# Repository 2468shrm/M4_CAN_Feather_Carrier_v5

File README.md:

# M4_CAN_Feather_Carrier_v5

## Board Layout

## Changes from Previous M4 Carrier Boards

This board has undergone multiple changes from previous versions of thie board, including, but not limite to:
- The level shifter for the DIOs was changed to the TXS0104B from the TXB version
  - The TXS version includes built-in pull ups and works considerably more reliably
- LEDs were added to indicate the logical state of the DIOs
  - An LED was added to each DIO as well as the level shifter enable
- The unity gain opamp was chaged to the LMV324AIDR which is a rail-to-rail version of the prior opamp
- One Qwiic/STEMMA port is removed (leaving 3)
- A MicroSD socket is added and extended to the SPI network (which now comprises of the Ethernet FeatherWing and the MicroS socket)
- A DC-DC converter is adde to the PCB replacing the Weewoodday module (woohoo)
- Cost reduced
  - Replaced many components with JLCPCB "Basic Parts" to reduce the Extended Parts costs
  - Many are 0603 devices for use with JLCPCB's PCBA service
- Updated the silkscreen to congratulate Unni Peri's graduation (the team will miss her contributions in the future, we're sure)

A PDF copy of the schematic [here](https://github.com/2468shrm/M4_CAN_Feather_Carrier_v3/blob/main/Images/Schematic.pdf).

## Checkout Status

This board has bot been fabbed yet.

Not yet tested:
- Everything :)

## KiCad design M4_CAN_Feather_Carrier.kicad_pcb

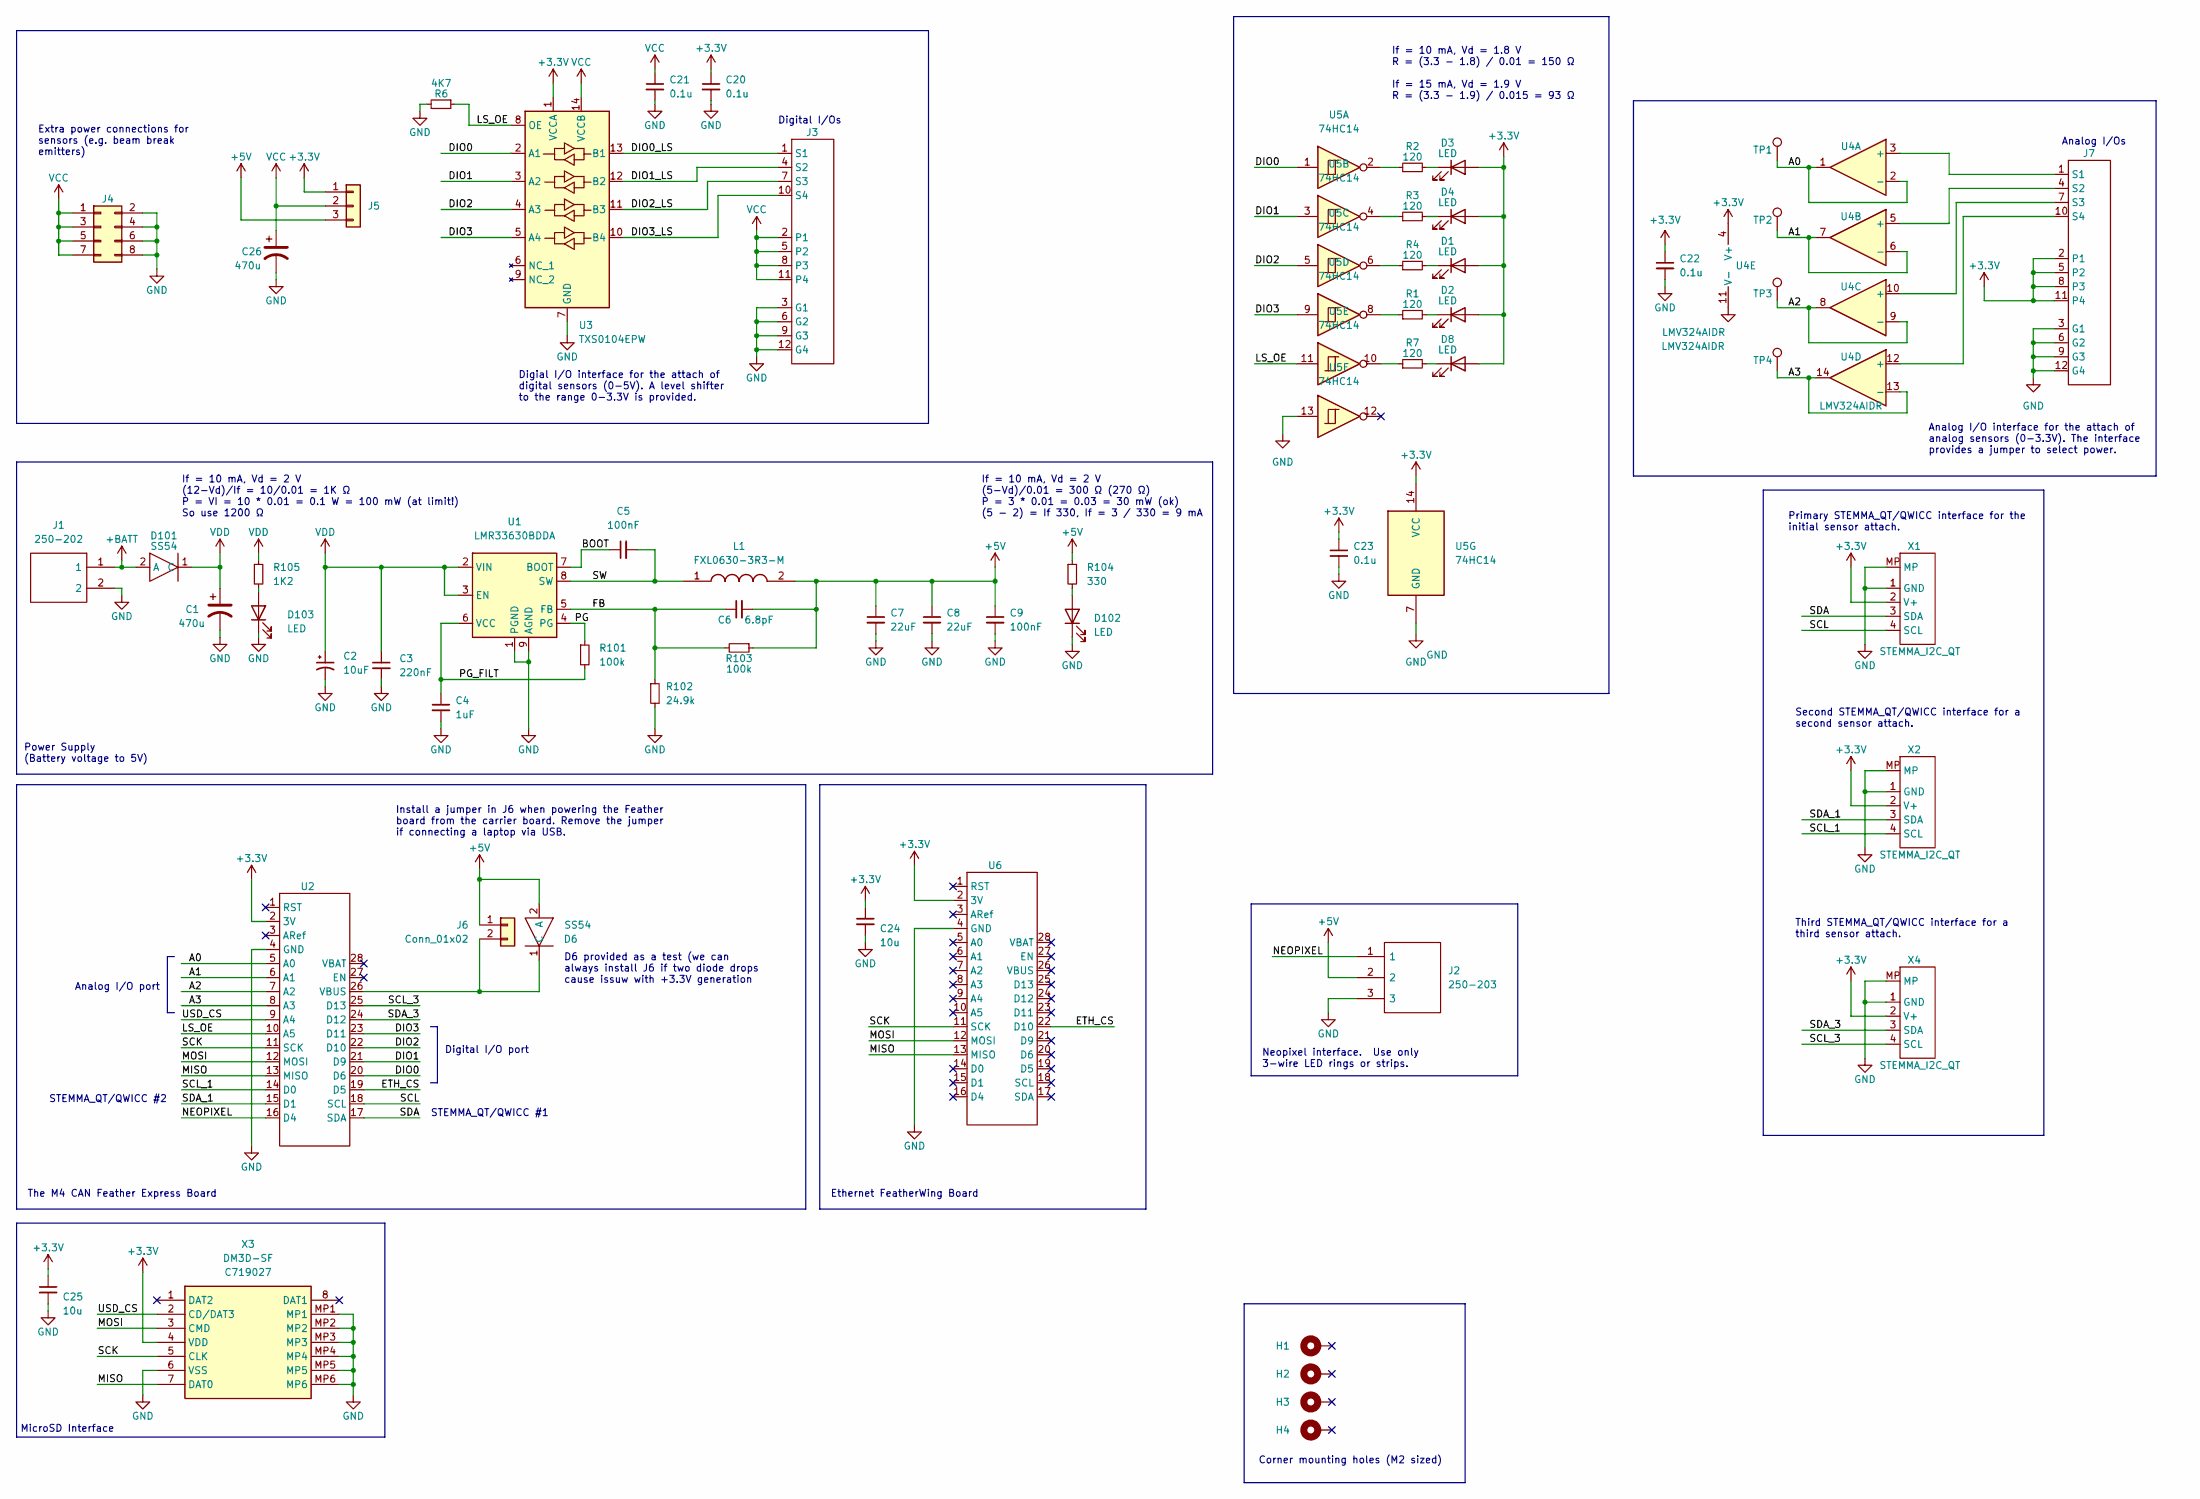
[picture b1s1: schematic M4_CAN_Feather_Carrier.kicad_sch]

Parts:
C1, C26: 470u; CAPAE830X1050N; LCSC C340767
C2: 10uF; C_0603_1608Metric; LCSC C96446
C3: 220nF; C_0603_1608Metric; LCSC C21120
C4: 1uF; C_0603_1608Metric; LCSC C59302
C5, C9: 100nF; C_0603_1608Metric; LCSC C14663
C6: 6.8pF; C_0603_1608Metric; LCSC C1679
C7, C8: 22uF; C_0805_2012Metric; LCSC C45783
C20, C21, C22, C23: 0.1u; C_0603_1608Metric; LCSC C14663
C24, C25: 10u; C_0603_1608Metric; LCSC C96446
D1, D2, D3, D4, D8, D102, D103: LED; LED_0603_1608Metric; LCSC C2286
D6, D101: SS54; DO-214AC; LCSC C22452
H1, H2, H3, H4: MountingHole_Pad; MountingHole_2.2mm_M2_DIN965_Pad
J1: 250-202; 250202; Manufacturer_Part_Number 250-202
J2: 250-203; 250-203_1; Manufacturer_Part_Number 250-203
J3, J7: conn_04_03; conn_04x03
J4: Conn_02x04_Odd_Even; PinHeader_2x04_P2.54mm_Vertical
J5: Conn_01x03; PinHeader_1x03_P2.54mm_Vertical
J6: Conn_01x02; PinHeader_1x02_P2.54mm_Vertical
L1: FXL0630-3R3-M; FXL0630; Manufacturer_Part_Number ASPI-0804T-150M-T; LCSC C167219
R1, R2, R3, R4, R7: 120; R_0603_1608Metric; LCSC C22787
R6: 4K7; R_0603_1608Metric; LCSC C23162
R101, R103: 100k; R_0603_1608Metric; LCSC C25803
R102: 24.9k; R_0603_1608Metric; LCSC C25962
R104: 330; R_0603_1608Metric; LCSC C23138
R105: 1K2; R_0603_1608Metric; LCSC C22765
TP1, TP2, TP3, TP4: TestPoint; TestPoint_Pad_1.5x1.5mm
U1: LMR33630BDDA; Texas_HSOP-8-1EP_3.9x4.9mm_P1.27mm_ThermalVias; LCSC C544370
U2, U6: Feather_M4_CAN_Express
U3: TXS0104EPW; TSSOP-14_4.4x5mm_P0.65mm; LCSC C44955
U4: LMV324AIDR; SOIC-14_3.9x8.7mm_P1.27mm; LCSC C484732
U5: 74HC14; TSSOP-14_4.4x5mm_P0.65mm; LCSC C2866133
X1, X2, X4: STEMMA_I2C_QT; JST_SH_BM04B-SRSS-TB_1x04-1MP_P1.00mm_Vertical; LCSC C495539
X3: DM3D-SF; DM3DSF; Manufacturer_Part_Number DM3D-SF; Mouser Part Number 798-DM3D-SF

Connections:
+3.3V: C20.1, C22.1, C23.1, C24.1, C25.1, D1.2 (A), D2.2 (A), D3.2 (A), D4.2 (A), D8.2 (A), J5.1, J7.2 (P1), J7.5 (P2), J7.8 (P3), J7.11 (P4), U2.2 (3V), U3.1 (VCCA), U4.4 (V+), U5.14 (VCC), U6.2 (3V), X1.2 (V+), X2.2 (V+), X3.4 (VDD), X4.2 (V+)
+5V: C6.2, C7.1, C8.1, C9.1, D6.2 (A), J2.2, J5.3, J6.1, L1.2, R103.1, R104.1
+BATT: D101.2 (A), J1.1
/A0: TP1.1, U2.5 (A0), U4.1, U4.2 (-)
/A1: TP2.1, U2.6 (A1), U4.6 (-), U4.7
/A2: TP3.1, U2.7 (A2), U4.8, U4.9 (-)
/A3: TP4.1, U2.8 (A3), U4.13 (-), U4.14
/BOOT: C5.1, U1.7 (BOOT)
/DIO0: U2.20 (D6), U3.2 (A1), U5.1
/DIO0_LS: J3.1 (S1), U3.13 (B1)
/DIO1: U2.21 (D9), U3.3 (A2), U5.3
/DIO1_LS: J3.4 (S2), U3.12 (B2)
/DIO2: U2.22 (D10), U3.4 (A3), U5.5
/DIO2_LS: J3.7 (S3), U3.11 (B3)
/DIO3: U2.23 (D11), U3.5 (A4), U5.9
/DIO3_LS: J3.10 (S4), U3.10 (B4)
/ETH_CS: U2.19 (D5), U6.22 (D10)
/FB: C6.1, R102.1, R103.2, U1.5 (FB)
/LS_OE: R6.1, U2.10 (A5), U3.8 (OE), U5.11
/MISO: U2.13 (MISO), U6.13 (MISO), X3.7 (DAT0)
/MOSI: U2.12 (MOSI), U6.12 (MOSI), X3.3 (CMD)
/NEOPIXEL: J2.1, U2.16 (D4)
/PG: R101.1, U1.4 (PG)
/PG_FILT: C4.1, R101.2, U1.6 (VCC)
/SCK: U2.11 (SCK), U6.11 (SCK), X3.5 (CLK)
/SCL: U2.18 (SCL), X1.4 (SCL)
/SCL_1: U2.14 (D0), X2.4 (SCL)
/SCL_3: U2.25 (D13), X4.4 (SCL)
/SDA: U2.17 (SDA), X1.3 (SDA)
/SDA_1: U2.15 (D1), X2.3 (SDA)
/SDA_3: U2.24 (D12), X4.3 (SDA)
/SW: C5.2, L1.1, U1.8 (SW)
/USD_CS: U2.9 (A4), X3.2 (CD/DAT3)
GND: C1.2, C2.2, C3.2, C4.2, C7.2, C8.2, C9.2, C20.2, C21.2, C22.2, C23.2, C24.2, C25.2, C26.2, D102.1 (K), D103.1 (K), J1.2, J2.3, J3.3 (G1), J3.6 (G2), J3.9 (G3), J3.12 (G4), J4.2, J4.4, J4.6, J4.8, J7.3 (G1), J7.6 (G2), J7.9 (G3), J7.12 (G4), R6.2, R102.2, U1.1 (PGND), U1.9 (AGND), U2.4 (GND), U3.7 (GND), U4.11 (V-), U5.7 (GND), U5.13, U6.4 (GND), X1.1 (GND), X1.MP, X2.1 (GND), X2.MP, X3.6 (VSS), X3.MP1, X3.MP2, X3.MP3, X3.MP4, X3.MP5, X3.MP6, X4.1 (GND), X4.MP
unnamed: D1.1 (K), R4.2
unnamed: D2.1 (K), R1.2
unnamed: D3.1 (K), R2.2
unnamed: D4.1 (K), R3.2
unnamed: D6.1 (C), J6.2, U2.26 (VBUS)
unnamed: D8.1 (K), R7.2
unnamed: D102.2 (A), R104.2
unnamed: D103.2 (A), R105.2
unnamed: J7.1 (S1), U4.3 (+)
unnamed: J7.4 (S2), U4.5 (+)
unnamed: J7.7 (S3), U4.10 (+)
unnamed: J7.10 (S4), U4.12 (+)
unnamed: R1.1, U5.8
unnamed: R2.1, U5.2
unnamed: R3.1, U5.4
unnamed: R4.1, U5.6
unnamed: R7.1, U5.10
VCC: C21.1, C26.1, J3.2 (P1), J3.5 (P2), J3.8 (P3), J3.11 (P4), J4.1, J4.3, J4.5, J4.7, J5.2, U3.14 (VCCB)
VDD: C1.1, C2.1, C3.1, D101.1 (C), R105.1, U1.2 (VIN), U1.3 (EN)

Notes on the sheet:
Corner mounting holes (M2 sized)
Digital I/Os
Install a jumper in J6 when powering the Feather board from the carrier board. Remove the jumper if connecting a laptop via USB.
Analog I/Os
Primary STEMMA_QT/QWICC interface for the initial sensor attach.
Extra power connections for sensors (e.g. beam break emitters)
Digial I/O interface for the attach of digital sensors (0-5V). A level shifter to the range 0-3.3V is provided.
The M4 CAN Feather Express Board
Second STEMMA_QT/QWICC interface for a second sensor attach.
If = 10 mA, Vd = 2 V (5-Vd)/0.01 = 300 Ω (270 Ω) P = 3 * 0.01 = 0.03 = 30 mW (ok) (5 - 2) = If 330, If = 3 / 330 = 9 mA
Digital I/O port
MicroSD Interface
Analog I/O port
STEMMA_QT/QWICC #1
If = 10 mA, Vd = 2 V (12-Vd)/If = 10/0.01 = 1K Ω P = VI = 10 * 0.01 = 0.1 W = 100 mW (at limit!) So use 1200 Ω
STEMMA_QT/QWICC #2
Analog I/O interface for the attach of analog sensors (0-3.3V). The interface provides a jumper to select power.
Neopixel interface. Use only 3-wire LED rings or strips.
Power Supply (Battery voltage to 5V)
Ethernet FeatherWing Board
D6 provided as a test (we can always install J6 if two diode drops cause issuw with +3.3V generation
Third STEMMA_QT/QWICC interface for a third sensor attach.
If = 10 mA, Vd = 1.8 V R = (3.3 - 1.8) / 0.01 = 150 Ω If = 15 mA, Vd = 1.9 V R = (3.3 - 1.9) / 0.015 = 93 Ω

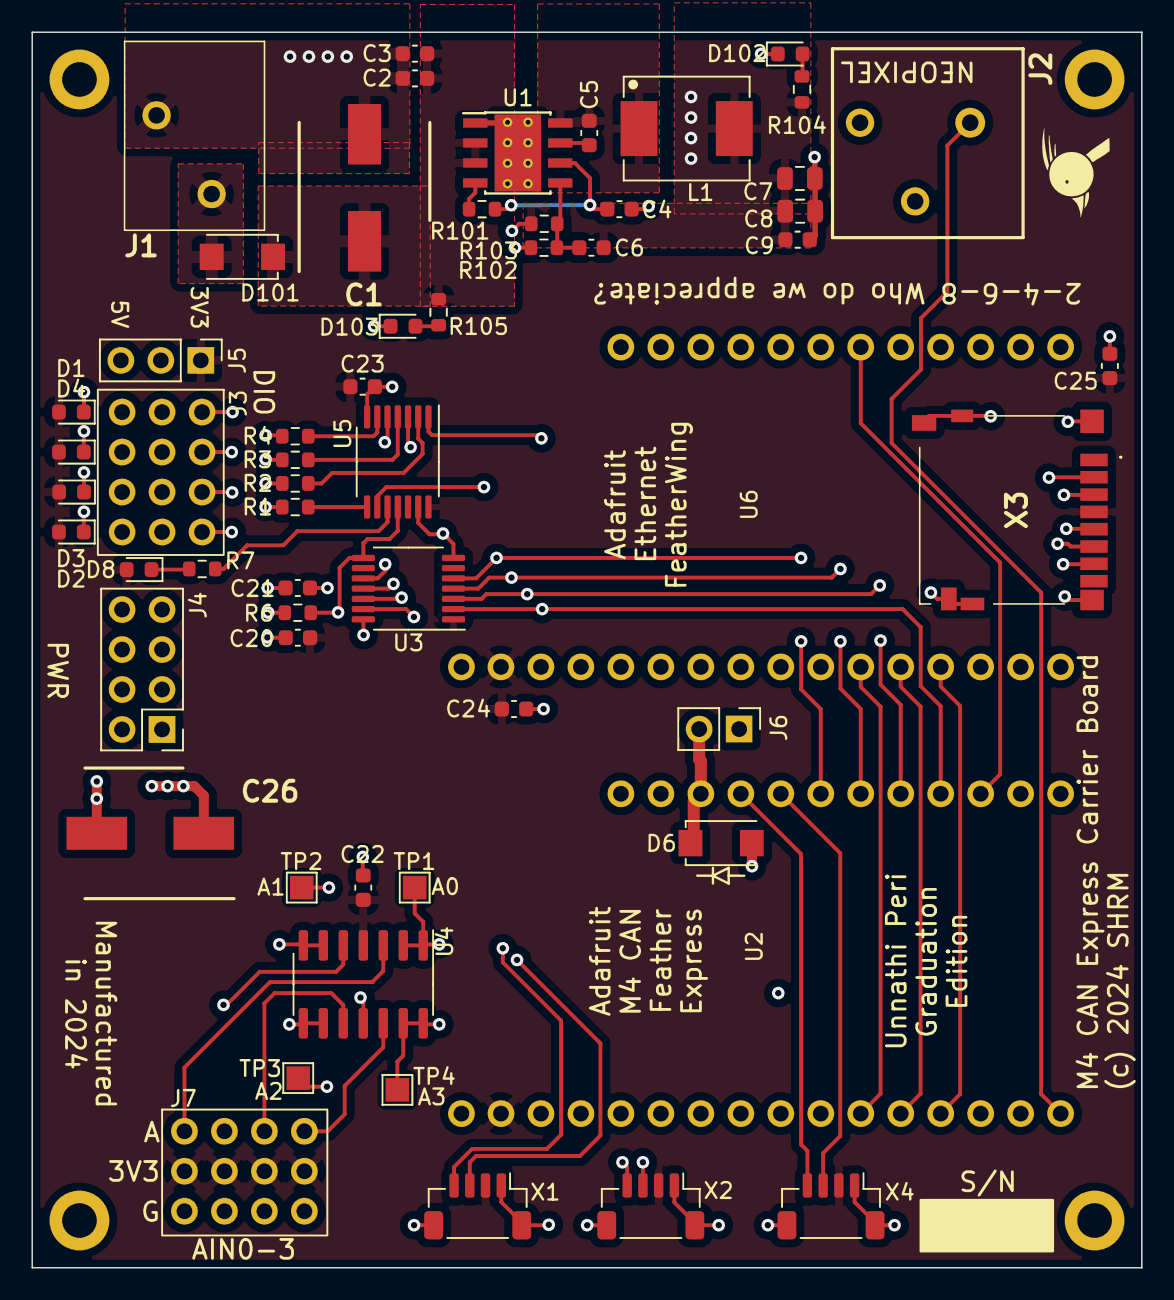
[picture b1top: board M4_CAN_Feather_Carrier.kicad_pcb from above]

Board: 4 copper layers, 70.5 x 78.5 mm, 62 parts (0 on the bottom side), 53 nets.

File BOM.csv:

Comment,Designator,Footprint,LCSC
"470u","C1","Appreciate:CAPAE830X1050N","C340767"
"470u","C26","Appreciate:CAPAE830X1050N","C340767"
"10uF","C2","Capacitor_SMD:C_0603_1608Metric","C96446"
"0.1u","C20","Capacitor_SMD:C_0603_1608Metric","C14663"
"0.1u","C21","Capacitor_SMD:C_0603_1608Metric","C14663"
"0.1u","C22","Capacitor_SMD:C_0603_1608Metric","C14663"
"0.1u","C23","Capacitor_SMD:C_0603_1608Metric","C14663"
"10u","C24","Capacitor_SMD:C_0603_1608Metric","C96446"
"10u","C25","Capacitor_SMD:C_0603_1608Metric","C96446"
"220nF","C3","Capacitor_SMD:C_0603_1608Metric","C21120"
"1uF","C4","Capacitor_SMD:C_0603_1608Metric","C59302"
"100nF","C5","Capacitor_SMD:C_0603_1608Metric","C14663"
"100nF","C9","Capacitor_SMD:C_0603_1608Metric","C14663"
"6.8pF","C6","Capacitor_SMD:C_0603_1608Metric","C1679"
"22uF","C7","Capacitor_SMD:C_0805_2012Metric","C45783"
"22uF","C8","Capacitor_SMD:C_0805_2012Metric","C45783"
"LED","D1","LED_SMD:LED_0603_1608Metric","C2286"
"LED","D2","LED_SMD:LED_0603_1608Metric","C2286"
"LED","D3","LED_SMD:LED_0603_1608Metric","C2286"
"LED","D4","LED_SMD:LED_0603_1608Metric","C2286"
"LED","D8","LED_SMD:LED_0603_1608Metric","C2286"
"LED","D102","LED_SMD:LED_0603_1608Metric","C2286"
"LED","D103","LED_SMD:LED_0603_1608Metric","C2286"
"SS54","D6","Appreciate:DO-214AC","C22452"
"SS54","D101","Appreciate:DO-214AC","C22452"
"FXL0630-3R3-M","L1","Appreciate:FXL0630","C167219"
"120","R1","Resistor_SMD:R_0603_1608Metric","C22787"
"120","R2","Resistor_SMD:R_0603_1608Metric","C22787"
"120","R3","Resistor_SMD:R_0603_1608Metric","C22787"
"120","R4","Resistor_SMD:R_0603_1608Metric","C22787"
"120","R7","Resistor_SMD:R_0603_1608Metric","C22787"
"100k","R101","Resistor_SMD:R_0603_1608Metric","C25803"
"100k","R103","Resistor_SMD:R_0603_1608Metric","C25803"
"24.9k","R102","Resistor_SMD:R_0603_1608Metric","C25962"
"330","R104","Resistor_SMD:R_0603_1608Metric","C23138"
"1K2","R105","Resistor_SMD:R_0603_1608Metric","C22765"
"4K7","R6","Resistor_SMD:R_0603_1608Metric","C23162"
"LMR33630BDDA","U1","Package_SO:Texas_HSOP-8-1EP_3.9x4.9mm_P1.27mm_ThermalVias","C544370"
"TXS0104EPW","U3","Package_SO:TSSOP-14_4.4x5mm_P0.65mm","C44955"
"LMV324AIDR","U4","Package_SO:SOIC-14_3.9x8.7mm_P1.27mm","C484732"
"74HC14","U5","Package_SO:TSSOP-14_4.4x5mm_P0.65mm","C2866133"
"STEMMA_I2C_QT","X1","Connector_JST:JST_SH_BM04B-SRSS-TB_1x04-1MP_P1.00mm_Vertical","C495539"
"STEMMA_I2C_QT","X2","Connector_JST:JST_SH_BM04B-SRSS-TB_1x04-1MP_P1.00mm_Vertical","C495539"
"STEMMA_I2C_QT","X4","Connector_JST:JST_SH_BM04B-SRSS-TB_1x04-1MP_P1.00mm_Vertical","C495539"
"DM3D-SF","X3","Appreciate:DM3DSF","C719027"

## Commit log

2024-06-17 board files (KiCAD)
2024-06-17 BOM and component position files for JLCPCB fabrication and assembly
2024-06-17 STEP file as generated by KiCAD

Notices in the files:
M4_CAN_Feather_Carrier.kicad_pcb:
All Rights Reserved
(c) 2024 SHRM
